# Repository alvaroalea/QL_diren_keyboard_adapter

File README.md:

# DIREN Keyboard Interface Clone
A reverse engineering exercice using the Diren PS/2 Keyboard adapter for Sinclair QL

Licensed under Cern OHL-S - https://ohwr.org/cern_ohl_s_v2.txt

## WARNING: DO NOT USE THIS PROJECT IS NOT TESTED AND MISSING THINGS
This is not a functional item, it's only a exercice of reverse engineering to reinforce my skills in Kicad EDA Software.

This project was done using freely available pictures of the interface found on internet.

Schematic shall be correct, and pins are wired and the schematic has sense.

Also this project is completely useless without the firmware of the microcontroller.

## Firmware

This is what is expect on the firmware, is only my guest:

Firmware configure port B as input and assing a interrupt to the port

Normally only 1 of the lines as tied to 0V at the same time, to indicate the row of keyboard to read.

Firmware configure port C as input to have high impedance.

In the main loop a variable store the actual key pressed and the controls keys.

When a interrupt is detected, a look-up table determine if the key pressed (if any) is related to the port B line that trigged the interrupt.
If related, a second look-up table determine the port C line that need to be activate.
then reconfigure the KBO line as output and tie to 0V.

As soon as the Port B line go high, reconfigure again the KBO line as input.

In the main loop of the microcontroller, comunication with keyboard is done, and actual key is stored in a variable.
It also has in charge to decode de other input for configuration and do the keyboard traslation of other keys.

The first row of the keyboard is the special characters, shift, control and enter, that can be pressed with other keys at same time, they are managed in separate variables.

a 3rd table will translate the 102 keys of the AT keyboard into the 64 keys of the QL.

The first table will have at leas 64 position (one for QL key) and will be used as a mask for determine if any KBO line is used by it.

A second table of 64 positions will indicate the bit of port B that need to go down on key press.

In this way, only 230 bytes of ROM area used, and only 1 byte and 3 bits are used for the keys.

## Comparative

## Reference

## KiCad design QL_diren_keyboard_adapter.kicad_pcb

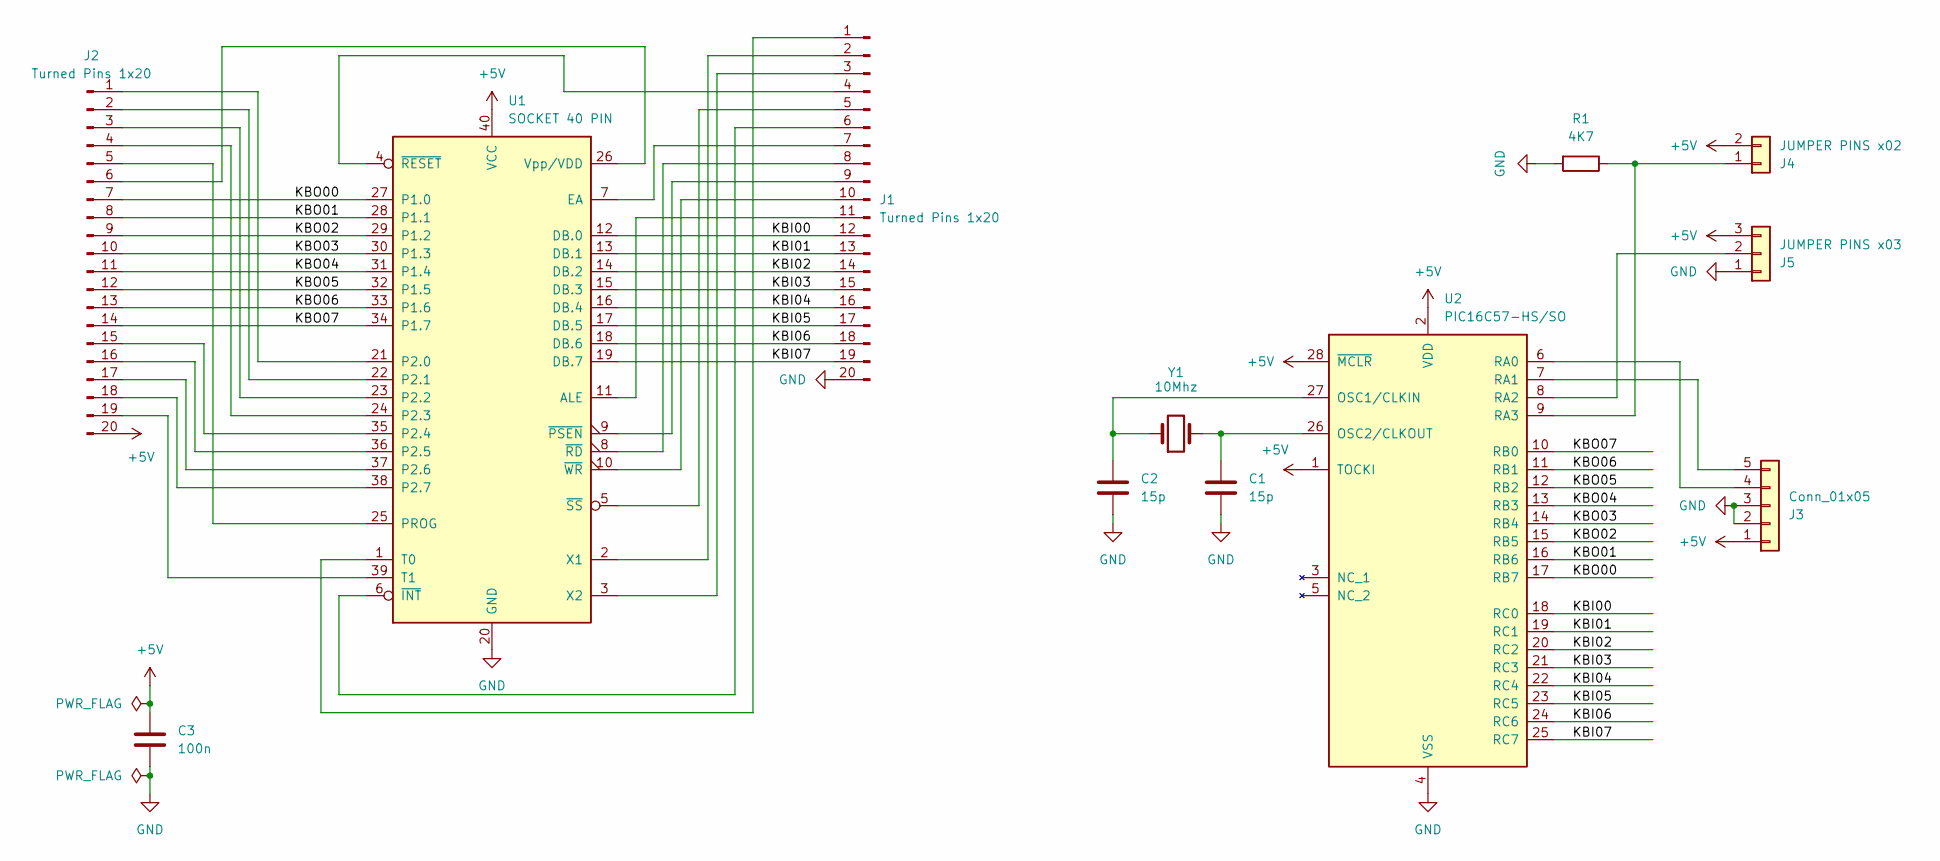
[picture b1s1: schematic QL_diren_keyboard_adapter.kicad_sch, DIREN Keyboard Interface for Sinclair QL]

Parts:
C1, C2: 15p; C_Disc_D4.3mm_W1.9mm_P5.00mm
C3: 100n; C_Disc_D4.3mm_W1.9mm_P5.00mm
J1, J2: Turned Pins 1x20; PinHeader_1x20_P2.54mm_Vertical
J3: Conn_01x05; PinHeader_1x05_P2.54mm_Horizontal
J4: JUMPER PINS x02; PinHeader_1x02_P2.54mm_Horizontal
J5: JUMPER PINS x03; PinHeader_1x03_P2.54mm_Horizontal
R1: 4K7; R_Axial_DIN0207_L6.3mm_D2.5mm_P7.62mm_Horizontal
U1: SOCKET 40 PIN; DIP-40_W15.24mm_Socket
U2: PIC16C57-HS/SO; SOIC-28W_7.5x17.9mm_P1.27mm
Y1: 10Mhz; Crystal_HC49-U_Horizontal

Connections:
+5V: C3.1, J2.20, J3.1, J4.2, J5.3, U1.40 (VCC), U2.1 (TOCKI), U2.2 (VDD), U2.28 (~MCLR)
/KBI00: J1.12, U1.12 (DB.0), U2.18 (RC0)
/KBI01: J1.13, U1.13 (DB.1), U2.19 (RC1)
/KBI02: J1.14, U1.14 (DB.2), U2.20 (RC2)
/KBI03: J1.15, U1.15 (DB.3), U2.21 (RC3)
/KBI04: J1.16, U1.16 (DB.4), U2.22 (RC4)
/KBI05: J1.17, U1.17 (DB.5), U2.23 (RC5)
/KBI06: J1.18, U1.18 (DB.6), U2.24 (RC6)
/KBI07: J1.19, U1.19 (DB.7), U2.25 (RC7)
/KBO00: J2.7, U1.27 (P1.0), U2.17 (RB7)
/KBO01: J2.8, U1.28 (P1.1), U2.16 (RB6)
/KBO02: J2.9, U1.29 (P1.2), U2.15 (RB5)
/KBO03: J2.10, U1.30 (P1.3), U2.14 (RB4)
/KBO04: J2.11, U1.31 (P1.4), U2.13 (RB3)
/KBO05: J2.12, U1.32 (P1.5), U2.12 (RB2)
/KBO06: J2.13, U1.33 (P1.6), U2.11 (RB1)
/KBO07: J2.14, U1.34 (P1.7), U2.10 (RB0)
GND: C1.2, C2.2, C3.2, J1.20, J3.2, J3.3, J5.1, R1.2, U1.20 (GND), U2.4 (VSS)
unnamed: J1.1, U1.1 (T0)
unnamed: J1.2, U1.2 (X1)
unnamed: J1.3, U1.3 (X2)
unnamed: J1.4, U1.4 (~RESET)
unnamed: J1.5, U1.5 (~SS)
unnamed: J1.6, U1.6 (~INT)
unnamed: J1.7, U1.7 (EA)
unnamed: J1.8, U1.8 (~RD)
unnamed: J1.9, U1.9 (~PSEN)
unnamed: J1.10, U1.10 (~WR)
unnamed: J1.11, U1.11 (ALE)
unnamed: J2.1, U1.21 (P2.0)
unnamed: J2.2, U1.22 (P2.1)
unnamed: J2.3, U1.23 (P2.2)
unnamed: J2.4, U1.24 (P2.3)
unnamed: J2.5, U1.25 (PROG)
unnamed: J2.6, U1.26 (Vpp/VDD)
unnamed: J2.15, U1.35 (P2.4)
unnamed: J2.16, U1.36 (P2.5)
unnamed: J2.17, U1.37 (P2.6)
unnamed: J2.18, U1.38 (P2.7)
unnamed: J2.19, U1.39 (T1)
unnamed: J3.4, U2.6 (RA0)
unnamed: J3.5, U2.7 (RA1)
unnamed: J4.1, R1.1, U2.9 (RA3)
unnamed: J5.2, U2.8 (RA2)
unnamed: C2.1, U2.27 (OSC1/CLKIN), Y1.1
unnamed: C1.1, U2.26 (OSC2/CLKOUT), Y1.2

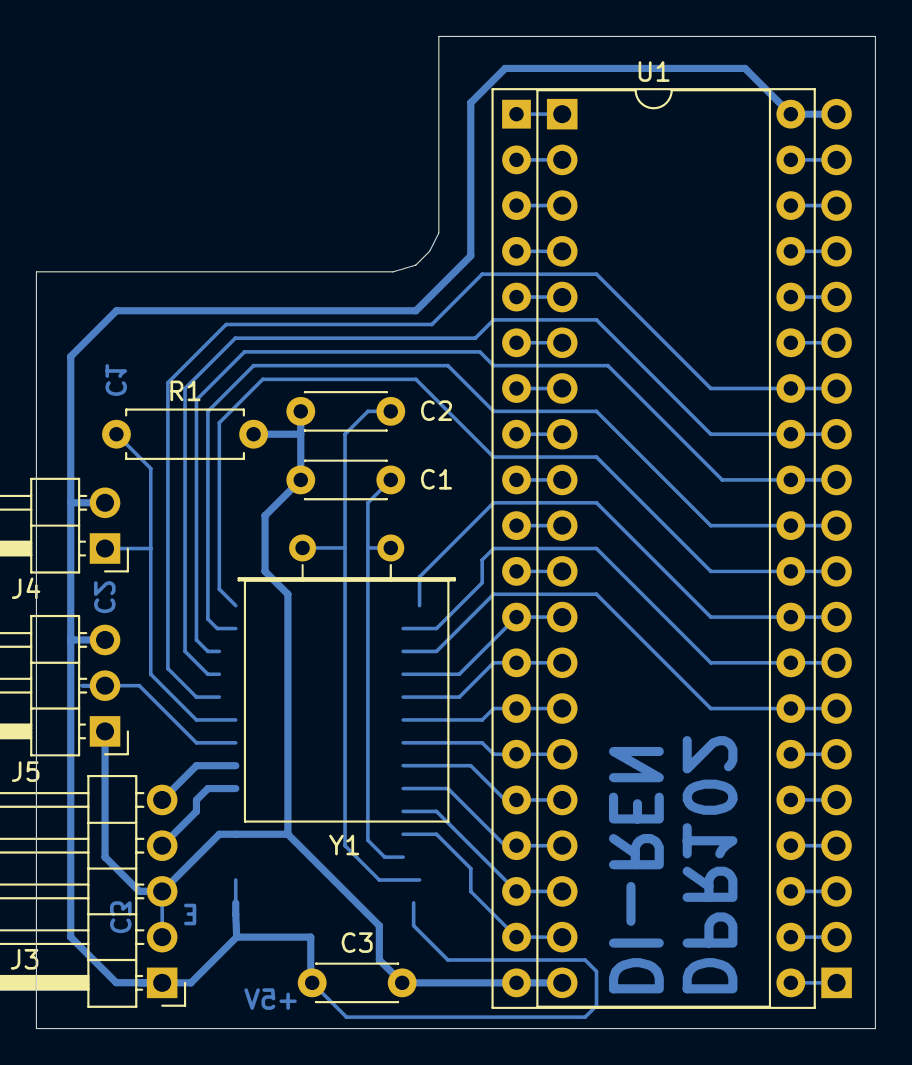
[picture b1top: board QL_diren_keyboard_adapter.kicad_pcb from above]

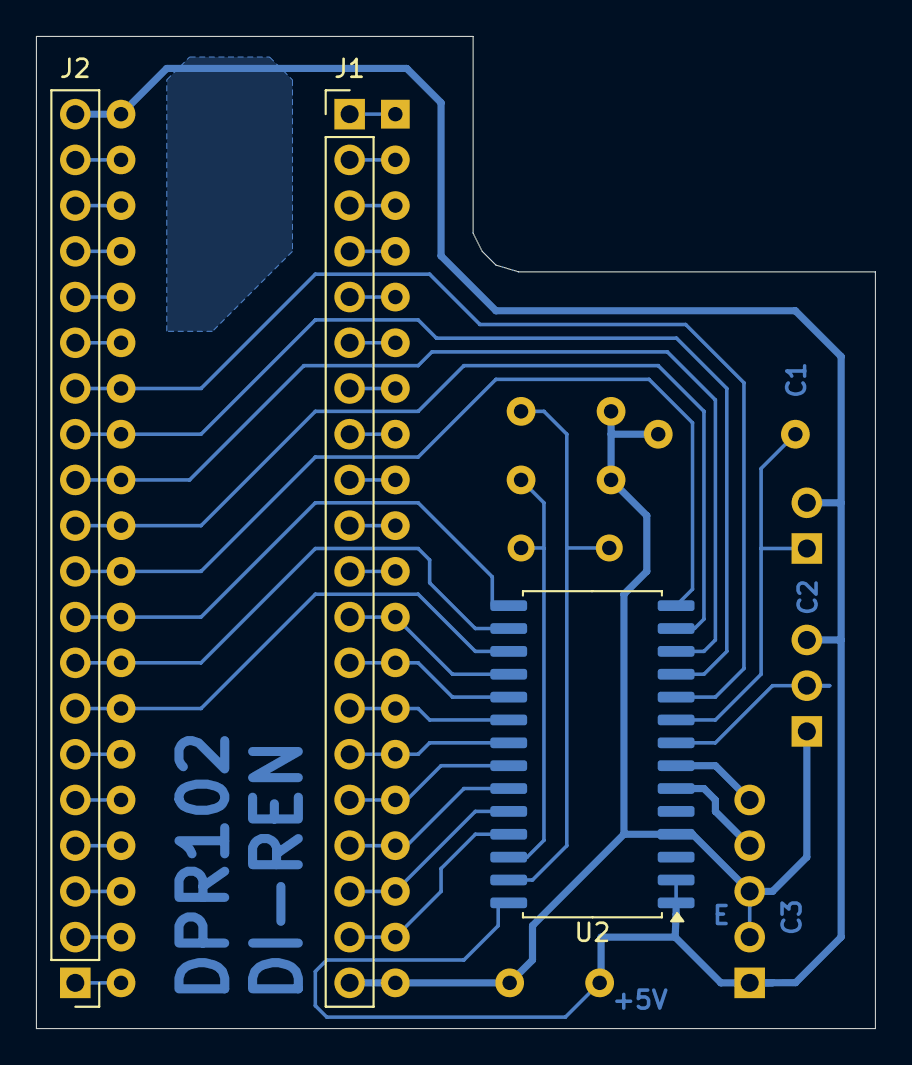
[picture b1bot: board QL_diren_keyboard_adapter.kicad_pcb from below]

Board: 2 copper layers, 46.6 x 55.1 mm, 12 parts (3 on the bottom side), 46 nets.

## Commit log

2024-07-30 initial
